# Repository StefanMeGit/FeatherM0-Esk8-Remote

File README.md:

# E-Skate Remote based on Feather M0
### Still in Development! 
Designed off of the Firefly remote by SolidGeek, this version of the remote has implemented a couple of new features- namely:
- Redesigned Shell- Shorther shell fits nicer into the hand
- Assorted Design Changes- Bearings on the moving parts, PCB based connections, and more!
- Feather M0 Architecture- Reliable connection thanks to the Feather M0 board, also allows for VESC data as before!
- Optional "Advanced" Reciever- Control your board's lighting! Headlights, Adaptive Tail Lights, or Stylelights! Anything up to 24w can be powered and activated from your remote! 
- Haptic Feedback- Now your remote can provide a vibration to physically alert you to predefined conditions (such as low battery)
- E-STOP- With E-STOP, you'll never have to worry about a runaway board! Although the remote shouldnt ever disconnect, in the event that is does, E-STOP will ensure that your board will slow down, instead of allowing the reciever to "lock open" at full throttle.
- Priority Transmission Handling- The remote will deactivate display refresh and UART pull if no valid transmission is received and prioritise transmission handling to ensure you remain in control!
- 3 Riding Modes- No matter if you're a Beginner, Intermediate, or Pro, the Feather Remote has got your back and will allow you to tame your board to your liking.
- Police Mode- Allows you to easily and secretly tame the power of your board...for whatever reason you may need
- Multifunction Trigger- Can be used as a Deadman switch, or to set Cruise Control! 

You can find the 3D-printable (STL) files for the remote on Thingiverse: https://www.thingiverse.com/thing:3321282
If you'd like, you can check out this project on the e-sk8 forums: https://www.electric-skateboard.builders/t/featherremote-and-smartremote/74084/18

The Intructions for the Remote can be found here: https://docs.google.com/document/d/17HkXw-V4jRMWkZ8O-B_I8DazQVeFwYYrkrsUbQE8zrY/edit?usp=sharing

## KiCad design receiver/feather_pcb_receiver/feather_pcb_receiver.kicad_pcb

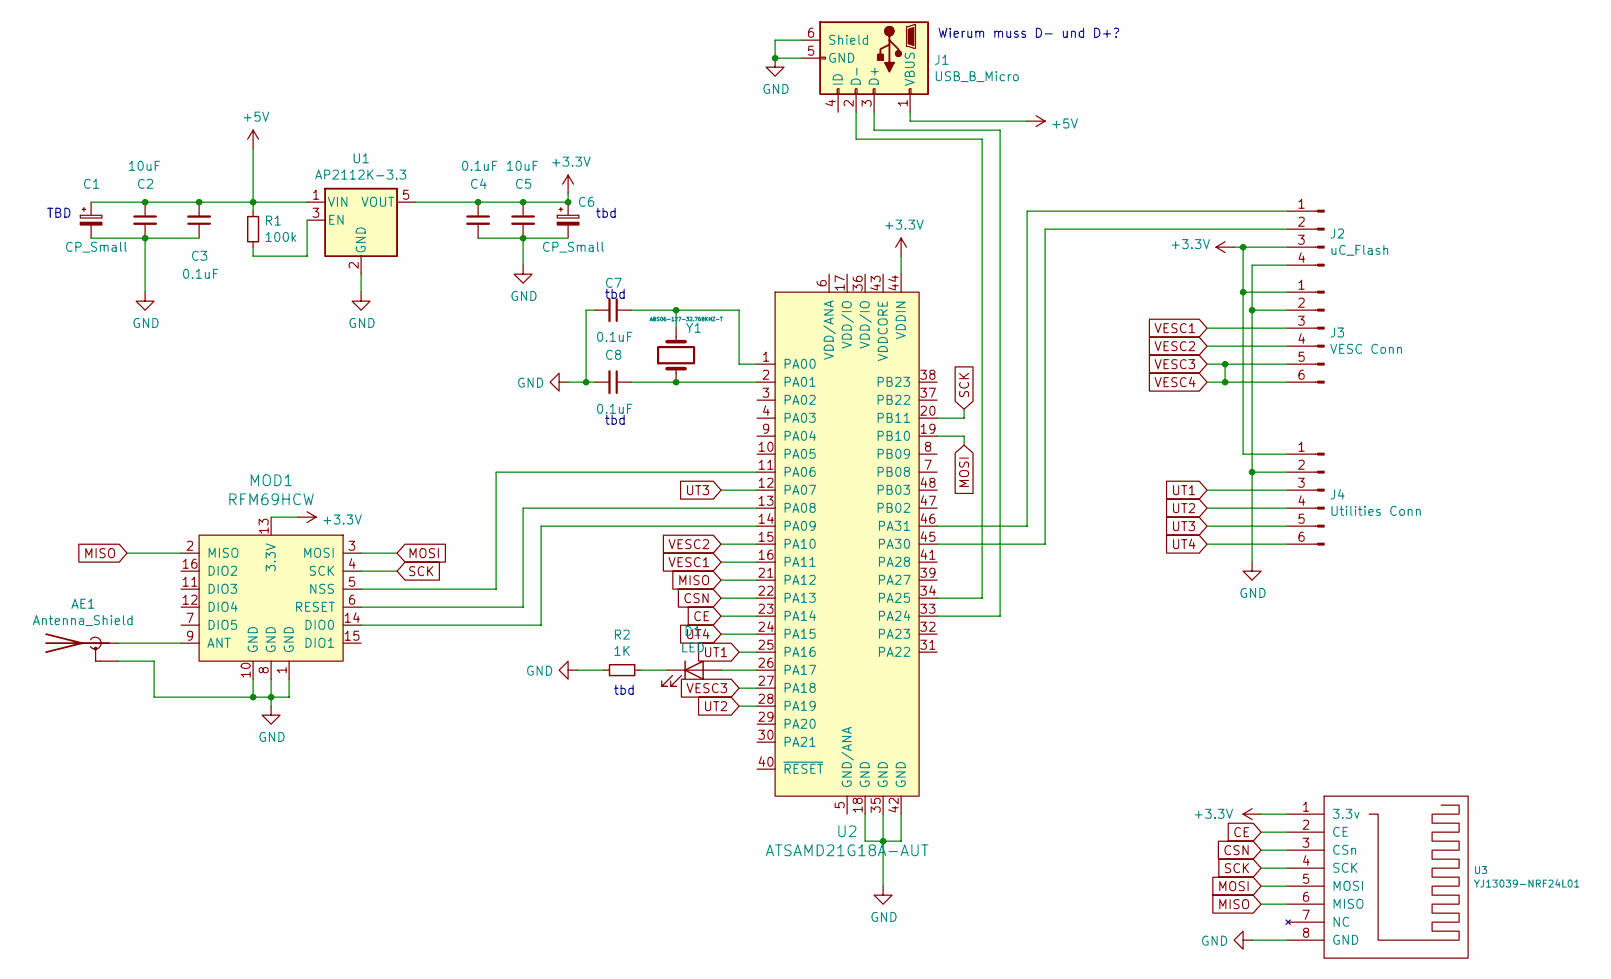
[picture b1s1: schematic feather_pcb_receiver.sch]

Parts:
AE1: Antenna_Shield; U.FL_Hirose_U.FL-R-SMT-1_Vertical
C1, C6: CP_Small; C_1206_3216Metric
C2, C5: 10uF; C_1206_3216Metric
C3, C4, C7, C8: 0.1uF; C_0805_2012Metric
D1: LED; LED_0805_2012Metric
J1: USB_B_Micro; USB_Micro-B_Molex-105017-0001
J2: uC_Flash; PinHeader_1x04_P2.00mm_Vertical
J3: VESC Conn; MICRO_JST_6
J4: Utilities Conn; MICRO_JST_6
MOD1: RFM69HCW; RF_Module_COM-13909; MPN COM-13909; Digi-Key_PN 1568-1394-ND
R1: 100k; R_0805_2012Metric
R2: 1K; R_0805_2012Metric
U1: AP2112K-3.3; SOT-23-5
U2: ATSAMD21G18A-AUT; TQFP-48_7x7mm; MPN ATSAMD21G18A-AUT; Digi-Key_PN ATSAMD21G18A-AUTCT-ND
U3: YJ13039-NRF24L01; YJ-13039-NRF24L01
Y1: ABS06-127-32.768KHZ-T‎; Crystal_SMD_2012-2Pin_2.0x1.2mm

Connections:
+3V3: C4.1, C5.1, C6.1, J2.3, J3.1, J4.1, MOD1.13 (3.3V), U1.5 (VOUT), U2.44 (VDDIN), U3.1 (3.3v)
+5V: C1.1, C2.1, C3.2, J1.1 (VBUS), R1.1, U1.1 (VIN)
CE: U2.23 (PA14), U3.2 (CE)
CSN: U2.22 (PA13), U3.3 (CSn)
GND: AE1.2 (Shield), C1.2, C2.2, C3.1, C4.2, C5.2, C6.2, C7.2, C8.2, J1.5 (GND), J1.6 (Shield), J2.4, J3.2, J4.2, MOD1.1 (GND), MOD1.8 (GND), MOD1.10 (GND), R2.2, U1.2 (GND), U2.18 (GND), U2.35 (GND), U2.42 (GND), U3.8 (GND)
MISO: MOD1.2 (MISO), U2.21 (PA12), U3.6 (MISO)
MOSI: MOD1.3 (MOSI), U2.19 (PB10), U3.5 (MOSI)
unnamed: AE1.1 (A), MOD1.9 (ANT)
unnamed: C7.1, U2.1 (PA00), Y1.2
unnamed: C8.1, U2.2 (PA01), Y1.1
unnamed: D1.1 (K), R2.1
unnamed: D1.2 (A), U2.26 (PA17)
unnamed: J1.2 (D-), U2.34 (PA25)
unnamed: J1.3 (D+), U2.33 (PA24)
unnamed: J2.1, U2.46 (PA31)
unnamed: J2.2, U2.45 (PA30)
unnamed: MOD1.5 (NSS), U2.11 (PA06)
unnamed: MOD1.6 (RESET), U2.13 (PA08)
unnamed: MOD1.14 (DIO0), U2.14 (PA09)
unnamed: R1.2, U1.3 (EN)
SCK: MOD1.4 (SCK), U2.20 (PB11), U3.4 (SCK)
UT1: J4.3, U2.25 (PA16)
UT2: J4.4, U2.28 (PA19)
UT3: J4.5, U2.12 (PA07)
UT4: J4.6, U2.24 (PA15)
VESC1: J3.3, U2.16 (PA11)
VESC2: J3.4, U2.15 (PA10)
VESC3: J3.5, J3.6, U2.27 (PA18)

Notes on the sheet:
Wierum muss D- und D+?
tbd
TBD

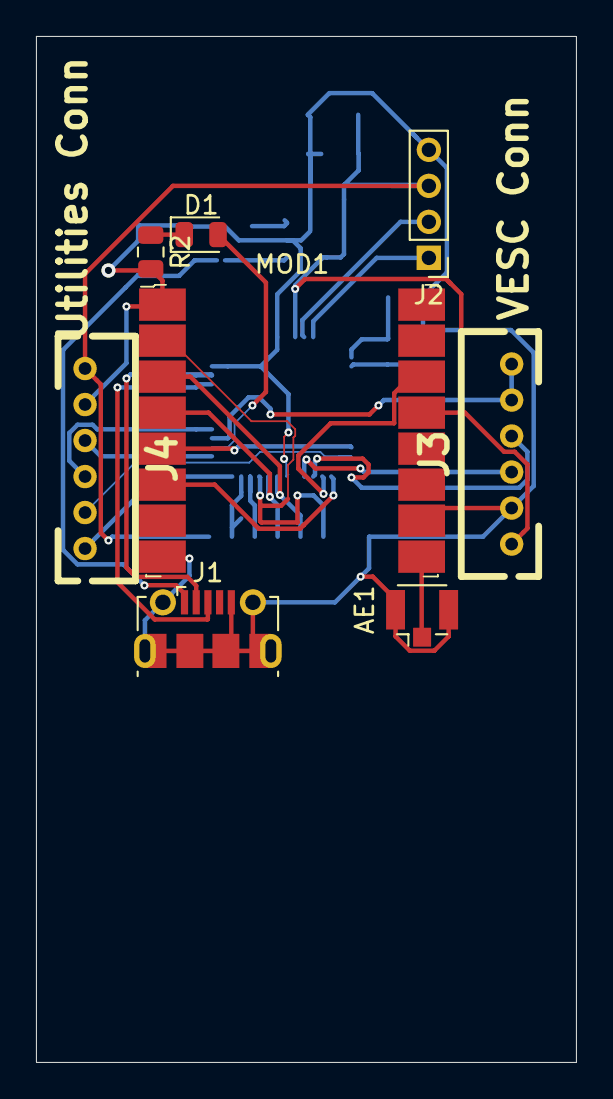
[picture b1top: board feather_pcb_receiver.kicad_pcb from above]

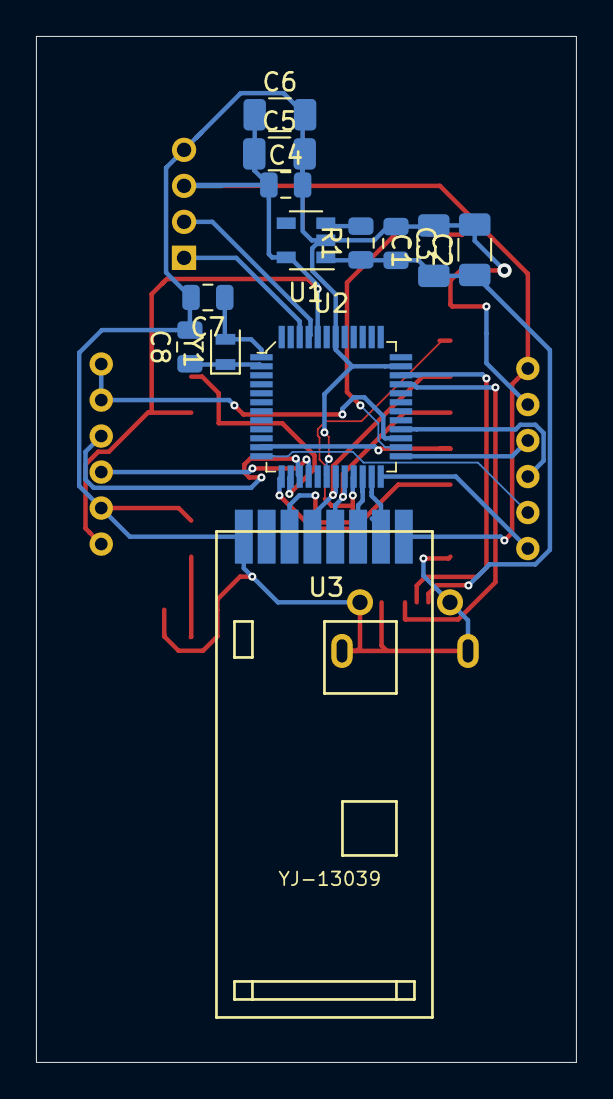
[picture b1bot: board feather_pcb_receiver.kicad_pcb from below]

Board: 2 copper layers, 30.0 x 57.0 mm, 21 parts (13 on the bottom side), 28 nets.

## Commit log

2018-10-04 Add second view for battery and motor current
    Decided to just make 2 views for now. One main view for riding with main SPEED value. Second for detailed view on battery voltage and current as well as motor current
2018-10-04 Updated for first and second view
    Decided to just make 2 views for now. One main view for riding with main SPEED value. Second for detailed view on battery voltage and current as well as motor current
2018-10-04 Bugfixing
    run through 2 views instead of 3
2018-10-04 Bugfixing
2018-10-04 Bugfix
2018-10-06 cleanup = extra button
    Cleanup and implement new method to check extra button state
2018-10-06 cleanup
    removed a lot of unnecessary variables
2018-10-06 arranged button handling new
2018-10-10 init FeatherM0 with RFM69
    First initiation with feather m0 and RFM60
2018-10-11 include addressed transmissions for RF69
2018-10-11 Revert "include addressed transmissions for RF69"
    This reverts commit 6c990e88ccc6512169769385364ae645443ab99a.
2018-10-11 Revert "Revert "include addressed transmissions for RF69""
    This reverts commit 5a9248b058ee9d0fa2187db7247de003c592cf13.
2018-10-11 Update to the newsest version of development
2018-10-13 Init RF69 communications
2018-10-15 Default Key to custom Key... not finished
2018-10-15 More work on handshake for encryptionkey handling...
2018-10-15 Debug
2018-10-15 improved flahs storage
2018-10-16 Udpated transmitSettingsToReceiver on transmittor side
2018-10-16 improve communication
2018-10-16 Milesstone! EncryptionKey
    First Milestone! Handshake of encryption key works!
2018-10-17 Update do settigns menu and handling board ids
    Need to test settings menu now!
2018-10-17 Retry test for safe shutdown
2018-10-17 Settings menu works and auto format
2018-10-17 PairBoard works
2018-10-17 Menu doesnt work correctly
2018-10-18 Settings
2018-10-18 Bugfix Settings
2018-10-19 Settings FirmVersion, EncyptionKez half
2018-10-19 Button press MEDIUM not working
2018-10-21 Debug view
2018-10-22 Rework rxSettings
2018-10-22 Working on trasmission stability
2018-10-23 CycleTimeTracking receiver
2018-10-23 update defineDEBUG
2018-10-24 UART VESC doesnt work
2018-10-24 DEBUG vesc uart
2018-10-24 Stable communication! 142ms max cycle time
2018-10-24 Display communication faster!
2018-10-24 Headlight implemenation
2018-10-24 logo
2018-10-25 WORKS
2018-10-25 Cycle time under 65ms
2018-10-25 UART activated
2018-10-25 fix to run without UART
2018-10-27 first Beta
2018-10-31 breaklight init
2018-11-01 implement adaptive Breaklight
2018-11-01 ESTOP implemented > 300ms
2018-11-01 update features
2018-11-02 Safety feature integrated
2018-11-03 Bugfix and menu
2018-11-03 Pairing fixed
2018-11-03 Paring works
    exept of first pairing, board goes in ESTOP, after turn off on everyting is ok
2018-11-11 backup..
2018-11-11 Backup Implement new menu things... not working correctly safety feature (strange throttle pos)
2018-11-12 Cleanup and ESTOP recover
2018-11-12 Estop recover testing
2018-11-12 bugfi8x
2018-11-12 WORKING
2018-11-13 Announcements implemented (not tested)
2018-11-13 improved announcements and combine them with vibration alarm
2018-11-13 Cleanup
2018-11-14 improved menu handling
2018-11-14 Frequency key added
2018-11-15 Stable
2018-11-16 Freq change does not work
2018-11-16 Sleep mode works
2018-11-16 bugfixing estop and standbymode in settings
2018-11-19 Test
2018-11-20 Solved problem with waiting receivers!
2018-11-20 Todo
2018-11-21 Unit selection and draw signal
2018-11-21 PoliceMode implemented
2018-11-22 Receiver Lite init
2018-11-22 Vib motor works with announcemnt
2018-11-23 Revert "Vib motor works with announcemnt"
    This reverts commit 4ef6879f54722138f460a1a6b62458c2c3be0afc.
2018-11-24 Cleanup and eStop deactivated
2018-11-24 Estop armed announcement
2018-11-24 Add last transmission duration to Estop announcement for debug
2018-11-26 initial tests stopeed, because of wrong voltage
2018-11-26 Add police man symbol and cleanup
2018-11-26 Optimize cycle time < 59ms
2018-11-26 Improve Estop handling BOTH MUST BE UPDATED!
2018-11-26 Bugfixing Estop arm
2018-11-26 update encryption key view in settings
2018-11-28 Metric/Imperial bugfix
2018-11-29 Bugfixing, Visual updates
2018-11-29 Update animations and announcements
2018-11-29 moved status down
2018-11-29 Estop with timer instead of counter, Automatic UART pull deactivation
2018-11-29 Announcement bugfix
2018-11-30 Update display refresh rate and samples
2018-12-01 GOLDEN MASTER!
2018-12-01 Shit
2018-12-01 added margin for breaklight
2018-12-01 recoverEstop bugfix
2018-12-03 estop update
2018-12-03 Estop Bugfixing
2018-12-03 Estop bugfix
2018-12-04 Bugfix estop / home screen
2018-12-04 update suffix on >99 values
2018-12-04 update battery level
2018-12-09 Update battery
2018-12-09 Join Settings bugfix
2018-12-27 bugfix paring, update breaklight
2018-12-27 Bugfix breaklight options
2018-12-27 update crusie control break
2018-12-27 Bugfix estop menu
2018-12-28 Update FeatureList
    grammar/spelling
2018-12-28 bugfix overcharge
    calculate overcharge limit to existing batteries regarding to txSettings.batteryCells
2019-01-05 Singal Lost bugfix
2019-01-06 make easier to choose frequecy / Bugfix join settings
2019-01-09 Estop Stability Test
2019-01-10 Unity support - not tried out!
2019-01-10 Init UNITY support
2019-01-10 Bugfix UART
2019-01-10 Page TEMP bugfix
2019-01-11 Bugfix EXIT menu - added dubbging for battery
2019-01-11 deactivate Voltage alarm in Settings
2019-01-11 Implement detailed page for UNITY support
2019-01-12 Bugfix UART pull for telemetry
2019-01-14 Deactivate DEBUG in default
2019-01-15 Update DEBUG
2019-01-16 extend debugging and bugfix
2019-01-18 Udpate dataPrefix for VESC
2019-01-19 UNITY telemetry display bugfix
2019-01-21 Bugfix checkBattery...
2019-01-23 extend DEBUGGING
2019-01-23 DISPLAY OFF for test
2019-02-08 changeSettings Bugfix
2019-02-08 Switch OFF display with HOLD TRIGGER and HOLD MENU BUTTON on startup
2019-02-08 deactivate DEBUG
2019-02-08 Activate encryption Key
2019-02-08 Bugfix DISPLAYOFF function
2019-02-08 Bugfixing RemoteBattery Alarm
2019-02-20 Activate Custom Key
2019-03-18 Extend RFM module debugging
2019-04-08 Make frequency adjustable
2019-04-08 Corrected screen rotation after sleep
2019-04-09 Test transmission modes
2019-04-09 Code improvement for transmissionMode
2019-04-09 init
2019-04-09 typo
2019-04-10 Add syncWord to rfm module
2019-04-10 Bugfix syncWord
2019-04-10 implement different modem configs
2019-04-11 Implement lostPackages counter
2019-04-11 No .DS_Store
2019-04-11 Remove already committed DS_Store
2019-05-09 added hardware for receiver
2019-05-10 replaced receiver eagle version with kicad
2019-05-10 removed eagle version and added connectors to kciad version
2019-05-14 added additional footprints and continued to layout
2019-06-10 Bugfix
    - remote battery
    - display frezze when not connected to receiver
2019-06-12 Implement thottle over UART
2019-06-13 Test SyncWord
2019-06-13 Update faster remote battery check on startup / cleanup
2019-06-14 Update UART pull when using ControlMode2
2019-06-14 UART only default
2019-06-14 Remote default UART only
2019-06-16 Implemnt throttle calibration menu
2019-06-17 rfm module layout
2019-06-17 implement throttle calibration menu
2019-06-17 new Menu
2019-06-17 added nrf module
2019-06-18 menu first phase
2019-06-18 work
2019-06-18 Update to PPM over UART
2019-06-18 corrct fscale for PCB choice
2019-06-21 Init new menu
2019-06-21 add comment
2019-06-23 bugfix because of newer version of ardunio ide
2019-06-26 beatify calib menu
2019-07-09 update to 14s
